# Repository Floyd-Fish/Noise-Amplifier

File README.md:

# Noise Amplifier

An ultra-low noise amplifier **(named EmoeNAP)** capable to measure low-noise LDO/OPA's wide band output noise, and many other interesting measurements. Referred to **[AN-159](https://www.analog.com/en/app-notes/an-159.html)**.

The full article about the initial version of Noise Amp can be found here:**[How to build a Noise Amplifier](https://www.emoe.xyz/noise-amplifier-building-instruction/)**. And to step further, to build the current version named **EmoeNAP**，please follow **[Noise Amplifier Step further](https://www.emoe.xyz/noise-amplifier-step-further/)**

Test result show that: with input shorted, the total output noise in 100kHz bandwidth is 1.76mVrms, and **the EmoeNAP's Gain equals to 80dB**, which results in **176nVrms input noise.**

Then connect a 50 ohms SMA Load to input, the total output noise in 100kHz bandwidth is 3.65mVrms, which equals in 365nVrms input noise.

A 50 ohms resistor's Johnson-Nyquist Noise(Themal noise) in 100kHz is 316nVrms(Theoretical), and 316nVrms combine with 176nVrms, resulting 361nVrms total output noise. This test verified the EmoeNAP's extraordinary ability to measure a 50 ohms resistor's Thermal Noise precisely.

# Still In Progress

**V2.3 has been verified but still needs improving.**    
In next version of EmoeNAP, I plan to change its architecture a little to the form below:

## V2.3 Known Issue

- Poor layout of output low-pass filter, to be re-designed.  
- Input Riso is not needed, because it introduces more thermal noise to input.(Can be seen as source impedance)  
- A resistor should be connected in series at wideband output port, because capacitive load( osilloscope input port, such as) can cause loop instability problem, so a resistor is needed to isolate the opamp output to load capacitor. A common value of 100 ohms is recommended.

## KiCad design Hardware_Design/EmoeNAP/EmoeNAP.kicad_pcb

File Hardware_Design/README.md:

# Hardware Specs

- NoiseAMP_BAT
> The battery pack for Noise Amplifier. Two 14500 Type 3.7V Li-ion Battery are used to provide ultralow power rail noise and high output current for NoiseAMP to work.

- NoiseAMP_V2.3(**Aborted**)
> The main PCB of the initial version of NoiseAMP, the current revision named EmoeNAP.

- EmoeNAP
> The current main PCB of NoiseAMP, called EmoeNAP, too.

To build a single cell EmoeNAP，**just use EmoeNAP is enough**.  
To build a 2-cell EmoeNAP, maybe you could have a look at NoiseAMP_BAT.

> Using one cell is more convenient to charge the battery, but will degrade noise performance a little bit.  
> Using two cell would get the best noise performance of EmoeNAP.

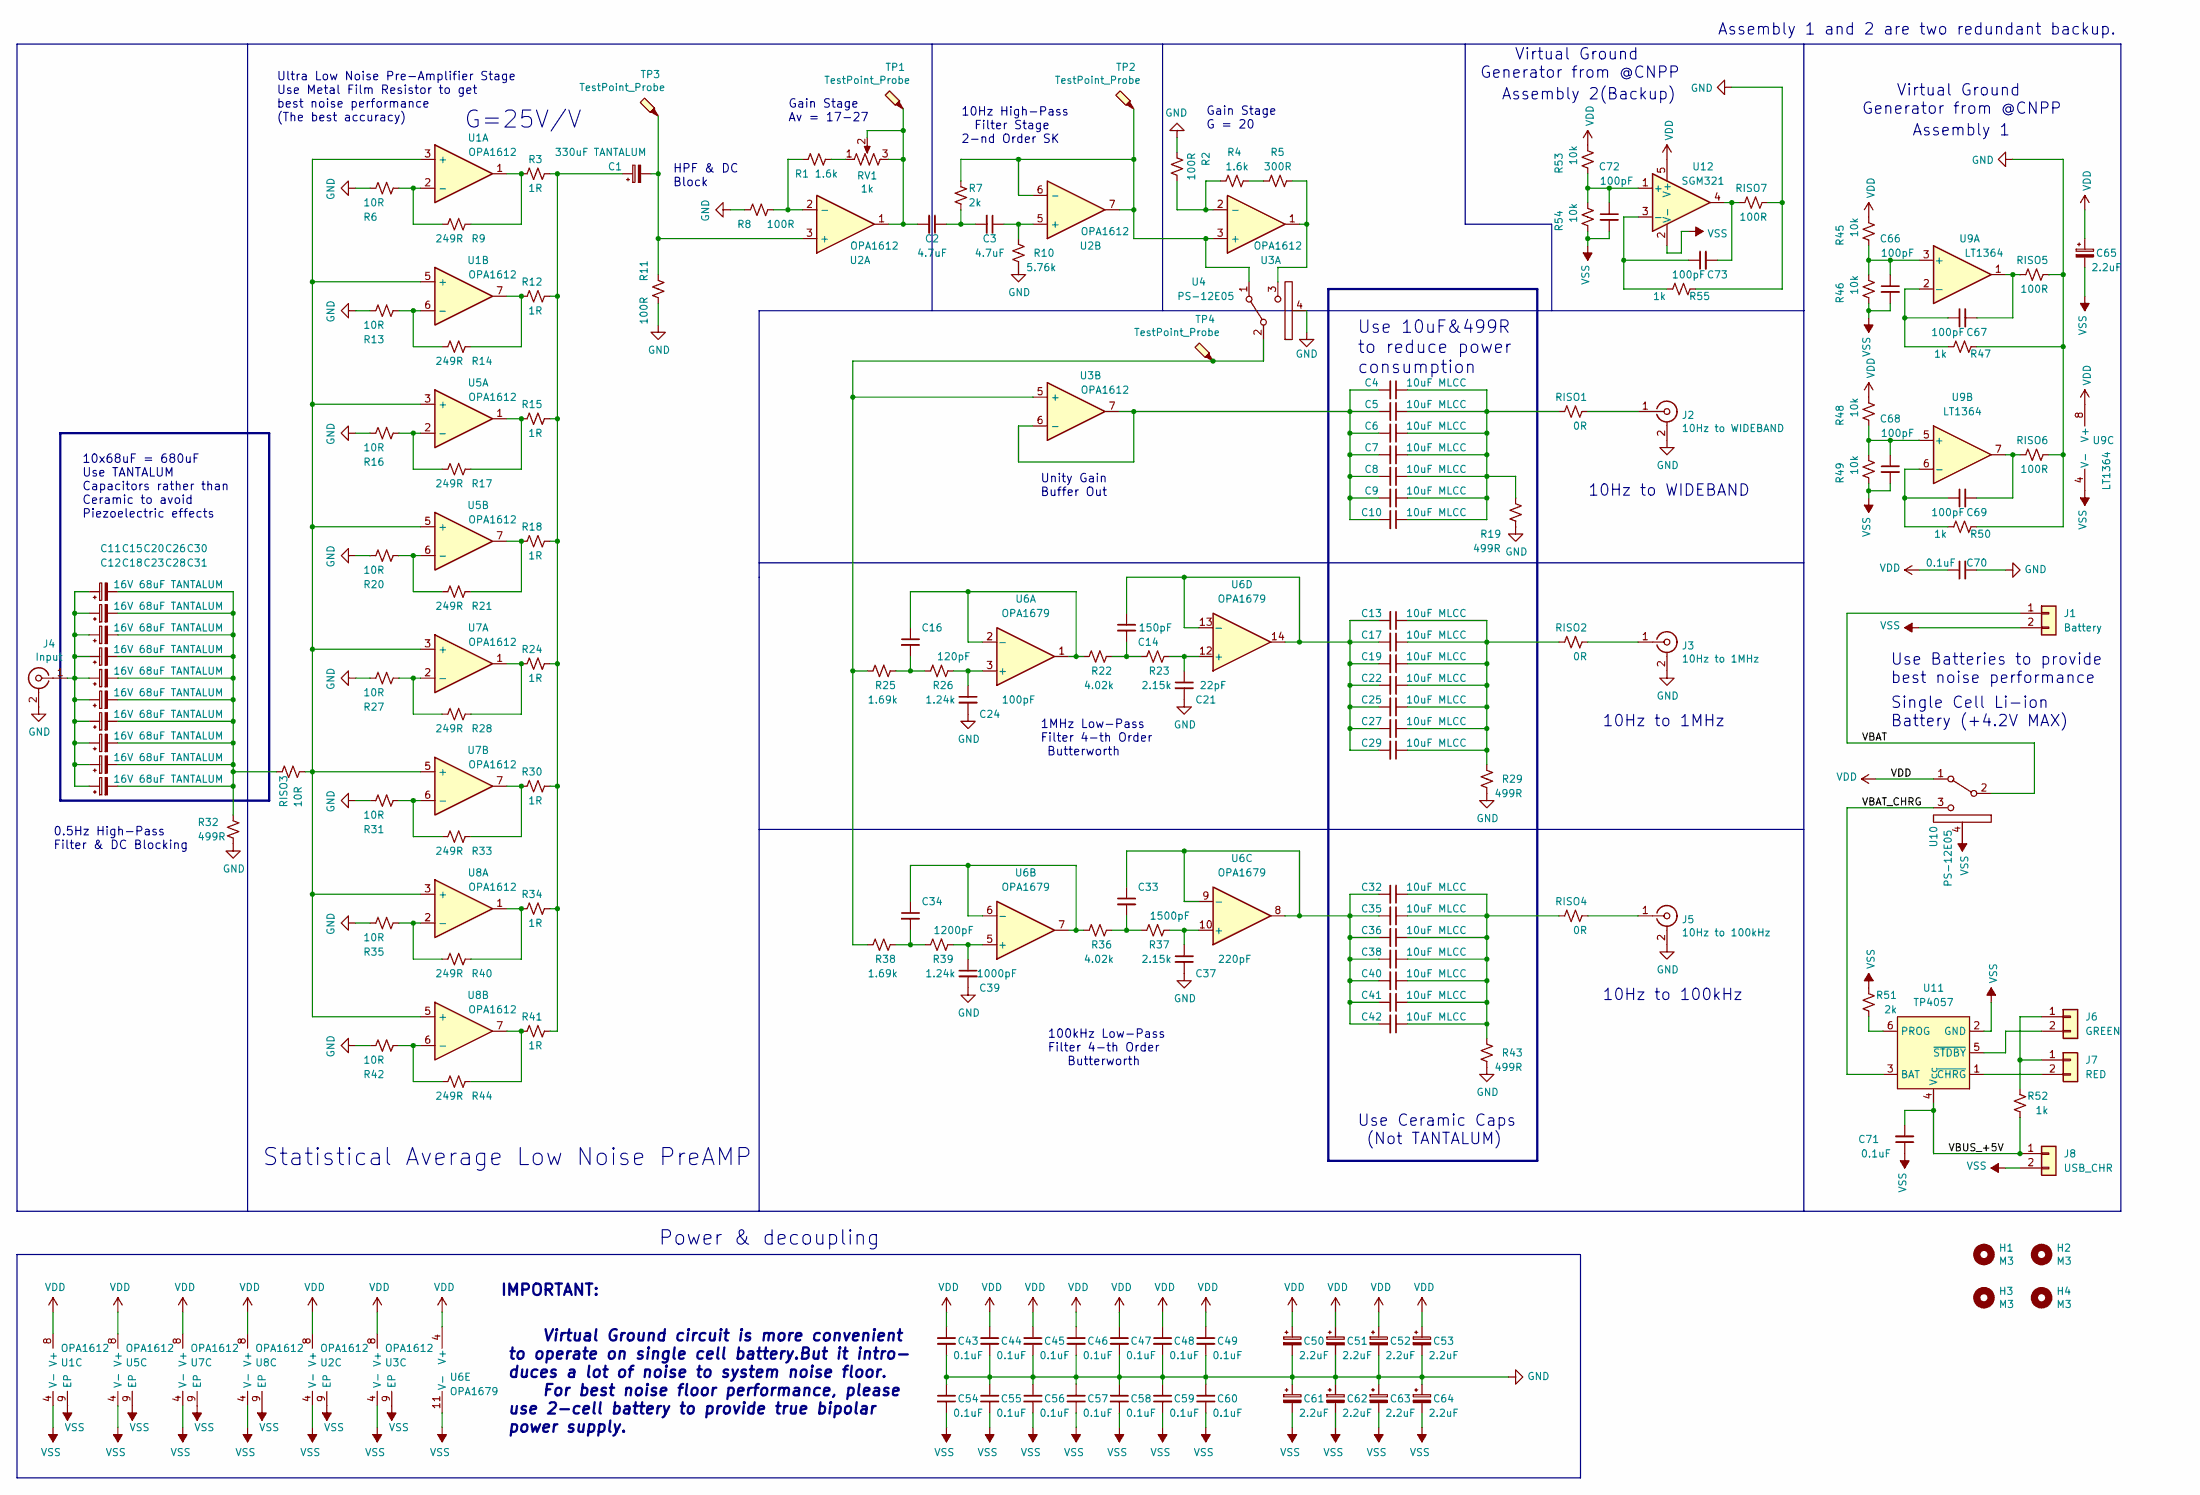
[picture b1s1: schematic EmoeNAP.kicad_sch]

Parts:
C1: 330uF TANTALUM; CP_EIA-6032-20_AVX-F
C2, C3: 4.7uF; C_0805_2012Metric
C4, C5, C6, C7, C8, C9, C10, C13, C17, C19, C22, C25, C27, C29, C32, C35, C36, C38, C40, C41, C42: 10uF MLCC; C_0805_2012Metric
C11, C12, C15, C18, C20, C23, C26, C28, C30, C31: 16V 68uF TANTALUM; CP_EIA-6032-20_AVX-F
C14: 150pF; C_0402_1005Metric
C16: 120pF; C_0402_1005Metric
C21: 22pF; C_0402_1005Metric
C24, C66, C67, C68, C69, C72, C73: 100pF; C_0402_1005Metric
C33: 1500pF; C_0402_1005Metric
C34: 1200pF; C_0402_1005Metric
C37: 220pF; C_0402_1005Metric
C39: 1000pF; C_0402_1005Metric
C43, C44, C45, C46, C47, C48, C49, C54, C55, C56, C57, C58, C59, C60, C70, C71: 0.1uF; C_0402_1005Metric
C50, C51, C52, C53, C61, C62, C63, C64, C65: 2.2uF; CP_EIA-3216-10_Kemet-I
H1, H2, H3, H4: M3; MountingHole_3.2mm_M3_Pad_TopOnly
J1: Battery; JST_XA_B02B-XASK-1_1x02_P2.50mm_Vertical
J2: 10Hz to WIDEBAND; U.FL_Molex_MCRF_73412-0110_Vertical
J3: 10Hz to 1MHz; U.FL_Molex_MCRF_73412-0110_Vertical
J4: Input; U.FL_Molex_MCRF_73412-0110_Vertical
J5: 10Hz to 100kHz; U.FL_Molex_MCRF_73412-0110_Vertical
J6: GREEN; TestPoint_2Pads_Pitch2.54mm_Drill0.8mm
J7: RED; TestPoint_2Pads_Pitch2.54mm_Drill0.8mm
J8: USB_CHR; JST_XA_B02B-XASK-1_1x02_P2.50mm_Vertical
R1, R4: 1.6k; R_0402_1005Metric
R2, R8, R11: 100R; R_0402_1005Metric
R3, R12, R15, R18, R24, R30, R34, R41: 1R; R_0402_1005Metric
R5: 300R; R_0402_1005Metric
R6, R13, R16, R20, R27, R31, R35, R42: 10R; R_0402_1005Metric
R7, R51: 2k; R_0402_1005Metric
R9, R14, R17, R21, R28, R33, R40, R44: 249R; R_0402_1005Metric
R10: 5.76k; R_0402_1005Metric
R19, R29, R32, R43: 499R; R_0805_2012Metric
R22, R36: 4.02k; R_0402_1005Metric
R23, R37: 2.15k; R_0402_1005Metric
R25, R38: 1.69k; R_0402_1005Metric
R26, R39: 1.24k; R_0402_1005Metric
R45, R46, R48, R49, R53, R54: 10k; R_0402_1005Metric
R47, R50, R52, R55: 1k; R_0402_1005Metric
RISO1, RISO2, RISO4: 0R; R_0805_2012Metric
RISO3: 10R; R_0805_2012Metric
RISO5, RISO6, RISO7: 100R; R_0603_1608Metric
RV1: 1k; Potentiometer_Bourns_3266W_Vertical
TP1, TP2, TP3, TP4: TestPoint_Probe; TestPoint_Pad_D1.0mm
U1, U2, U3, U5, U7, U8: OPA1612; WSON-8-1EP_3x3mm_P0.5mm_EP1.2x2mm
U4, U10: PS-12E05
U6: OPA1679; SOIC-14_3.9x8.7mm_P1.27mm
U9: LT1364; SOIC-8_3.9x4.9mm_P1.27mm
U11: TP4057; SOT-23-6
U12: SGM321; SOT-23-5

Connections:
/VBAT: J1.1, U10.2
/VBAT_CHRG: U10.3, U11.3 (BAT)
/VBUS_+5V: C71.2, J8.1, R52.1, U11.4 (Vcc)
GND: C21.2, C24.2, C37.2, C39.2, C43.2, C44.2, C45.2, C46.2, C47.2, C48.2, C49.2, C50.2, C51.2, C52.2, C53.2, C54.1, C55.1, C56.1, C57.1, C58.1, C59.1, C60.1, C61.1, C62.1, C63.1, C64.1, C70.2, J2.2 (Ext), J3.2 (Ext), J4.2 (Ext), J5.2 (Ext), R2.1, R6.2, R8.1, R10.2, R11.2, R13.2, R16.2, R19.2, R20.2, R27.2, R29.2, R31.2, R32.2, R35.2, R42.2, R43.2, R47.1, R50.1, R55.1, RISO5.2, RISO6.2, RISO7.2, U4.4
unnamed: C1.1, R3.2, R12.2, R15.2, R18.2, R24.2, R30.2, R34.2, R41.2
unnamed: C1.2, R11.1, TP3.1, U2.3 (+)
unnamed: C2.1, C3.2, R7.2
unnamed: C2.2, RV1.2, RV1.3, TP1.1, U2.1
unnamed: C3.1, R10.1, U2.5 (+)
unnamed: C4.1, C5.1, C6.1, C7.1, C8.1, C9.1, C10.1, R19.1, RISO1.1
unnamed: C4.2, C5.2, C6.2, C7.2, C8.2, C9.2, C10.2, U3.6 (-), U3.7
unnamed: C11.1, C12.1, C15.1, C18.1, C20.1, C23.1, C26.1, C28.1, C30.1, C31.1, J4.1 (In)
unnamed: C11.2, C12.2, C15.2, C18.2, C20.2, C23.2, C26.2, C28.2, C30.2, C31.2, R32.1, RISO3.1
unnamed: C13.1, C17.1, C19.1, C22.1, C25.1, C27.1, C29.1, R29.1, RISO2.1
unnamed: C13.2, C14.1, C17.2, C19.2, C22.2, C25.2, C27.2, C29.2, U6.13 (-), U6.14
unnamed: C14.2, R22.1, R23.2
unnamed: C16.1, R22.2, U6.1, U6.2 (-)
unnamed: C16.2, R25.1, R26.2
unnamed: C21.1, R23.1, U6.12 (+)
unnamed: C24.1, R26.1, U6.3 (+)
unnamed: C32.1, C35.1, C36.1, C38.1, C40.1, C41.1, C42.1, R43.1, RISO4.1
unnamed: C32.2, C33.1, C35.2, C36.2, C38.2, C40.2, C41.2, C42.2, U6.8, U6.9 (-)
unnamed: C33.2, R36.1, R37.2
unnamed: C34.1, R36.2, U6.6 (-), U6.7
unnamed: C34.2, R38.1, R39.2
unnamed: C37.1, R37.1, U6.10 (+)
unnamed: C39.1, R39.1, U6.5 (+)
unnamed: C66.1, R45.1, R46.2, U9.3 (+)
unnamed: C67.1, R47.2, U9.2 (-)
unnamed: C67.2, RISO5.1, U9.1
unnamed: C68.1, R48.1, R49.2, U9.5 (+)
unnamed: C69.1, R50.2, U9.6 (-)
unnamed: C69.2, RISO6.1, U9.7
unnamed: C72.1, R53.1, R54.2, U12.1 (+)
unnamed: C73.1, R55.2, U12.3 (-)
unnamed: C73.2, RISO7.1, U12.4
unnamed: J2.1 (In), RISO1.2
unnamed: J3.1 (In), RISO2.2
unnamed: J5.1 (In), RISO4.2
unnamed: J6.1, J7.1, R52.2
unnamed: J6.2, U11.5 (~STDBY)
unnamed: J7.2, U11.1 (~CHRG)
unnamed: R1.1, R8.2, U2.2 (-)
unnamed: R1.2, RV1.1
unnamed: R2.2, R4.1, U3.2 (-)
unnamed: R3.1, R9.1, U1.1
unnamed: R4.2, R5.1
unnamed: R5.2, U3.1, U4.3
unnamed: R6.1, R9.2, U1.2 (-)
unnamed: R7.1, TP2.1, U2.6 (-), U2.7, U3.3 (+), U4.1
unnamed: R12.1, R14.1, U1.7
unnamed: R13.1, R14.2, U1.6 (-)
unnamed: R15.1, R17.1, U5.1
unnamed: R16.1, R17.2, U5.2 (-)
unnamed: R18.1, R21.1, U5.7
unnamed: R20.1, R21.2, U5.6 (-)
unnamed: R24.1, R28.1, U7.1
unnamed: R25.2, R38.2, TP4.1, U3.5 (+), U4.2
unnamed: R27.1, R28.2, U7.2 (-)
unnamed: R30.1, R33.1, U7.7
unnamed: R31.1, R33.2, U7.6 (-)
unnamed: R34.1, R40.1, U8.1
unnamed: R35.1, R40.2, U8.2 (-)
unnamed: R41.1, R44.1, U8.7
unnamed: R42.1, R44.2, U8.6 (-)
unnamed: R51.1, U11.6 (PROG)
unnamed: RISO3.2, U1.3 (+), U1.5 (+), U5.3 (+), U5.5 (+), U7.3 (+), U7.5 (+), U8.3 (+), U8.5 (+)
VDD: C43.1, C44.1, C45.1, C46.1, C47.1, C48.1, C49.1, C50.1, C51.1, C52.1, C53.1, C65.1, C70.1, R45.2, R48.2, R53.2, U1.8 (V+), U2.8 (V+), U3.8 (V+), U5.8 (V+), U6.4 (V+), U7.8 (V+), U8.8 (V+), U9.8 (V+), U10.1, U12.5 (V+)
VSS: C54.2, C55.2, C56.2, C57.2, C58.2, C59.2, C60.2, C61.2, C62.2, C63.2, C64.2, C65.2, C66.2, C68.2, C71.1, C72.2, J1.2, J8.2, R46.1, R49.1, R51.2, R54.1, U1.4 (V-), U1.9 (EP), U2.4 (V-), U2.9 (EP), U3.4 (V-), U3.9 (EP), U5.4 (V-), U5.9 (EP), U6.11 (V-), U7.4 (V-), U7.9 (EP), U8.4 (V-), U8.9 (EP), U9.4 (V-), U10.4, U11.2 (GND), U12.2 (V-)

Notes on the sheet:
100kHz Low-Pass Filter 4-th Order Butterworth
Use 10uF&499R to reduce power consumption
Single Cell Li-ion Battery (+4.2V MAX)
0.5Hz High-Pass Filter & DC Blocking
10x68uF = 680uF Use TANTALUM Capacitors rather than Ceramic to avoid Piezoelectric effects
Statistical Average Low Noise PreAMP
G=25V/V
1MHz Low-Pass Filter 4-th Order Butterworth
HPF & DC Block
Virtual Ground Generator from @CNPP
10Hz to 100kHz
Assembly 2(Backup)
Use Batteries to provide best noise performance
10Hz High-Pass Filter Stage 2-nd Order SK
Power & decoupling
Unity Gain Buffer Out
IMPORTANT:
Ultra Low Noise Pre-Amplifier Stage Use Metal Film Resistor to get best noise performance (The best accuracy)
10Hz to 1MHz
Virtual Ground circuit is more convenient to operate on single cell battery.But it intro- duces a lot of noise to system noise floor. For best noise floor performance, please use 2-cell battery to provide true bipolar power supply.
10Hz to WIDEBAND
Use Ceramic Caps (Not TANTALUM)
Assembly 1 and 2 are two redundant backup.
Gain Stage G = 20
Gain Stage Av = 17-27
Assembly 1

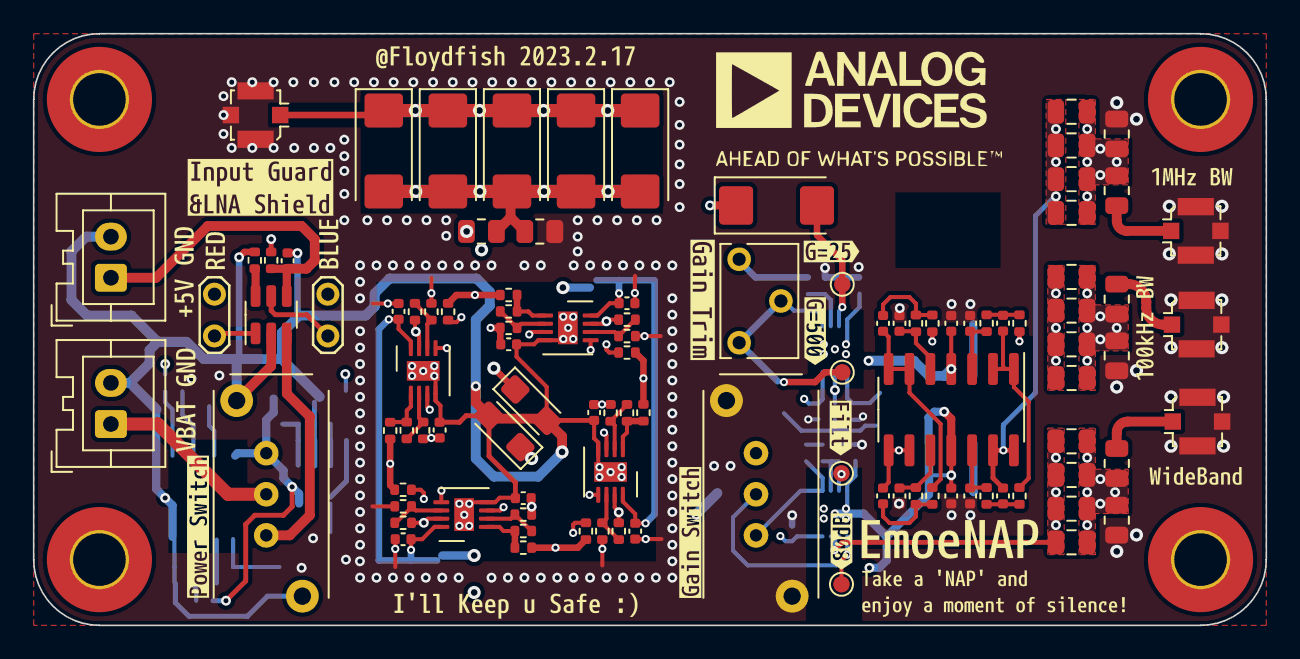
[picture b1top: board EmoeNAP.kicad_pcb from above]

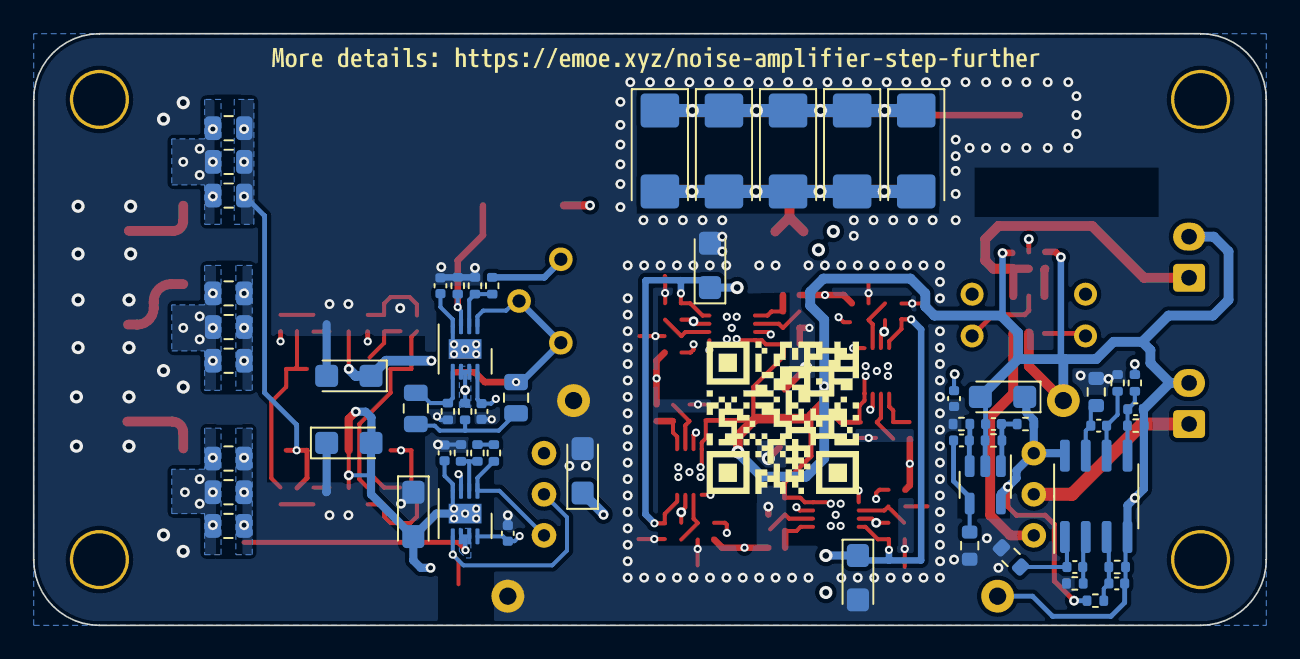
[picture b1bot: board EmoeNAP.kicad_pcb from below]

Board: 4 copper layers, 75.0 x 36.0 mm, 184 parts (59 on the bottom side), 69 nets.

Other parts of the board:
kibuzzard-63ED0A5F: G***; kibuzzard-63ED0A5F
kibuzzard-63EE51C1: G***; kibuzzard-63EE51C1
kibuzzard-63EE51DC: G***; kibuzzard-63EE51DC
kibuzzard-63EE53DB: G***; kibuzzard-63EE53DB
kibuzzard-63EE512D: G***; kibuzzard-63EE512D
kibuzzard-63EE520C: G***; kibuzzard-63EE520C
kibuzzard-63EE5216: G***; kibuzzard-63EE5216
kibuzzard-63EE5345: G***; kibuzzard-63EE5345
kibuzzard-6378A7DC: G***; kibuzzard-6378A7DC
kibuzzard-6378A7EA: G***; kibuzzard-6378A7EA
kibuzzard-6378A7F5: G***; kibuzzard-6378A7F5
kibuzzard-6378A8E8: G***; kibuzzard-6378A8E8
kibuzzard-6378A91A: G***; kibuzzard-6378A91A
kibuzzard-6378A94A: G***; kibuzzard-6378A94A
kibuzzard-6378A590: G***; kibuzzard-6378A590
kibuzzard-6378A691: G***; kibuzzard-6378A691
kibuzzard-6378A997: G***; kibuzzard-6378A997
kibuzzard-6378AA98: G***; kibuzzard-6378AA98
kibuzzard-6378AAC6: G***; kibuzzard-6378AAC6
kibuzzard-6378AB16: G***; kibuzzard-6378AB16

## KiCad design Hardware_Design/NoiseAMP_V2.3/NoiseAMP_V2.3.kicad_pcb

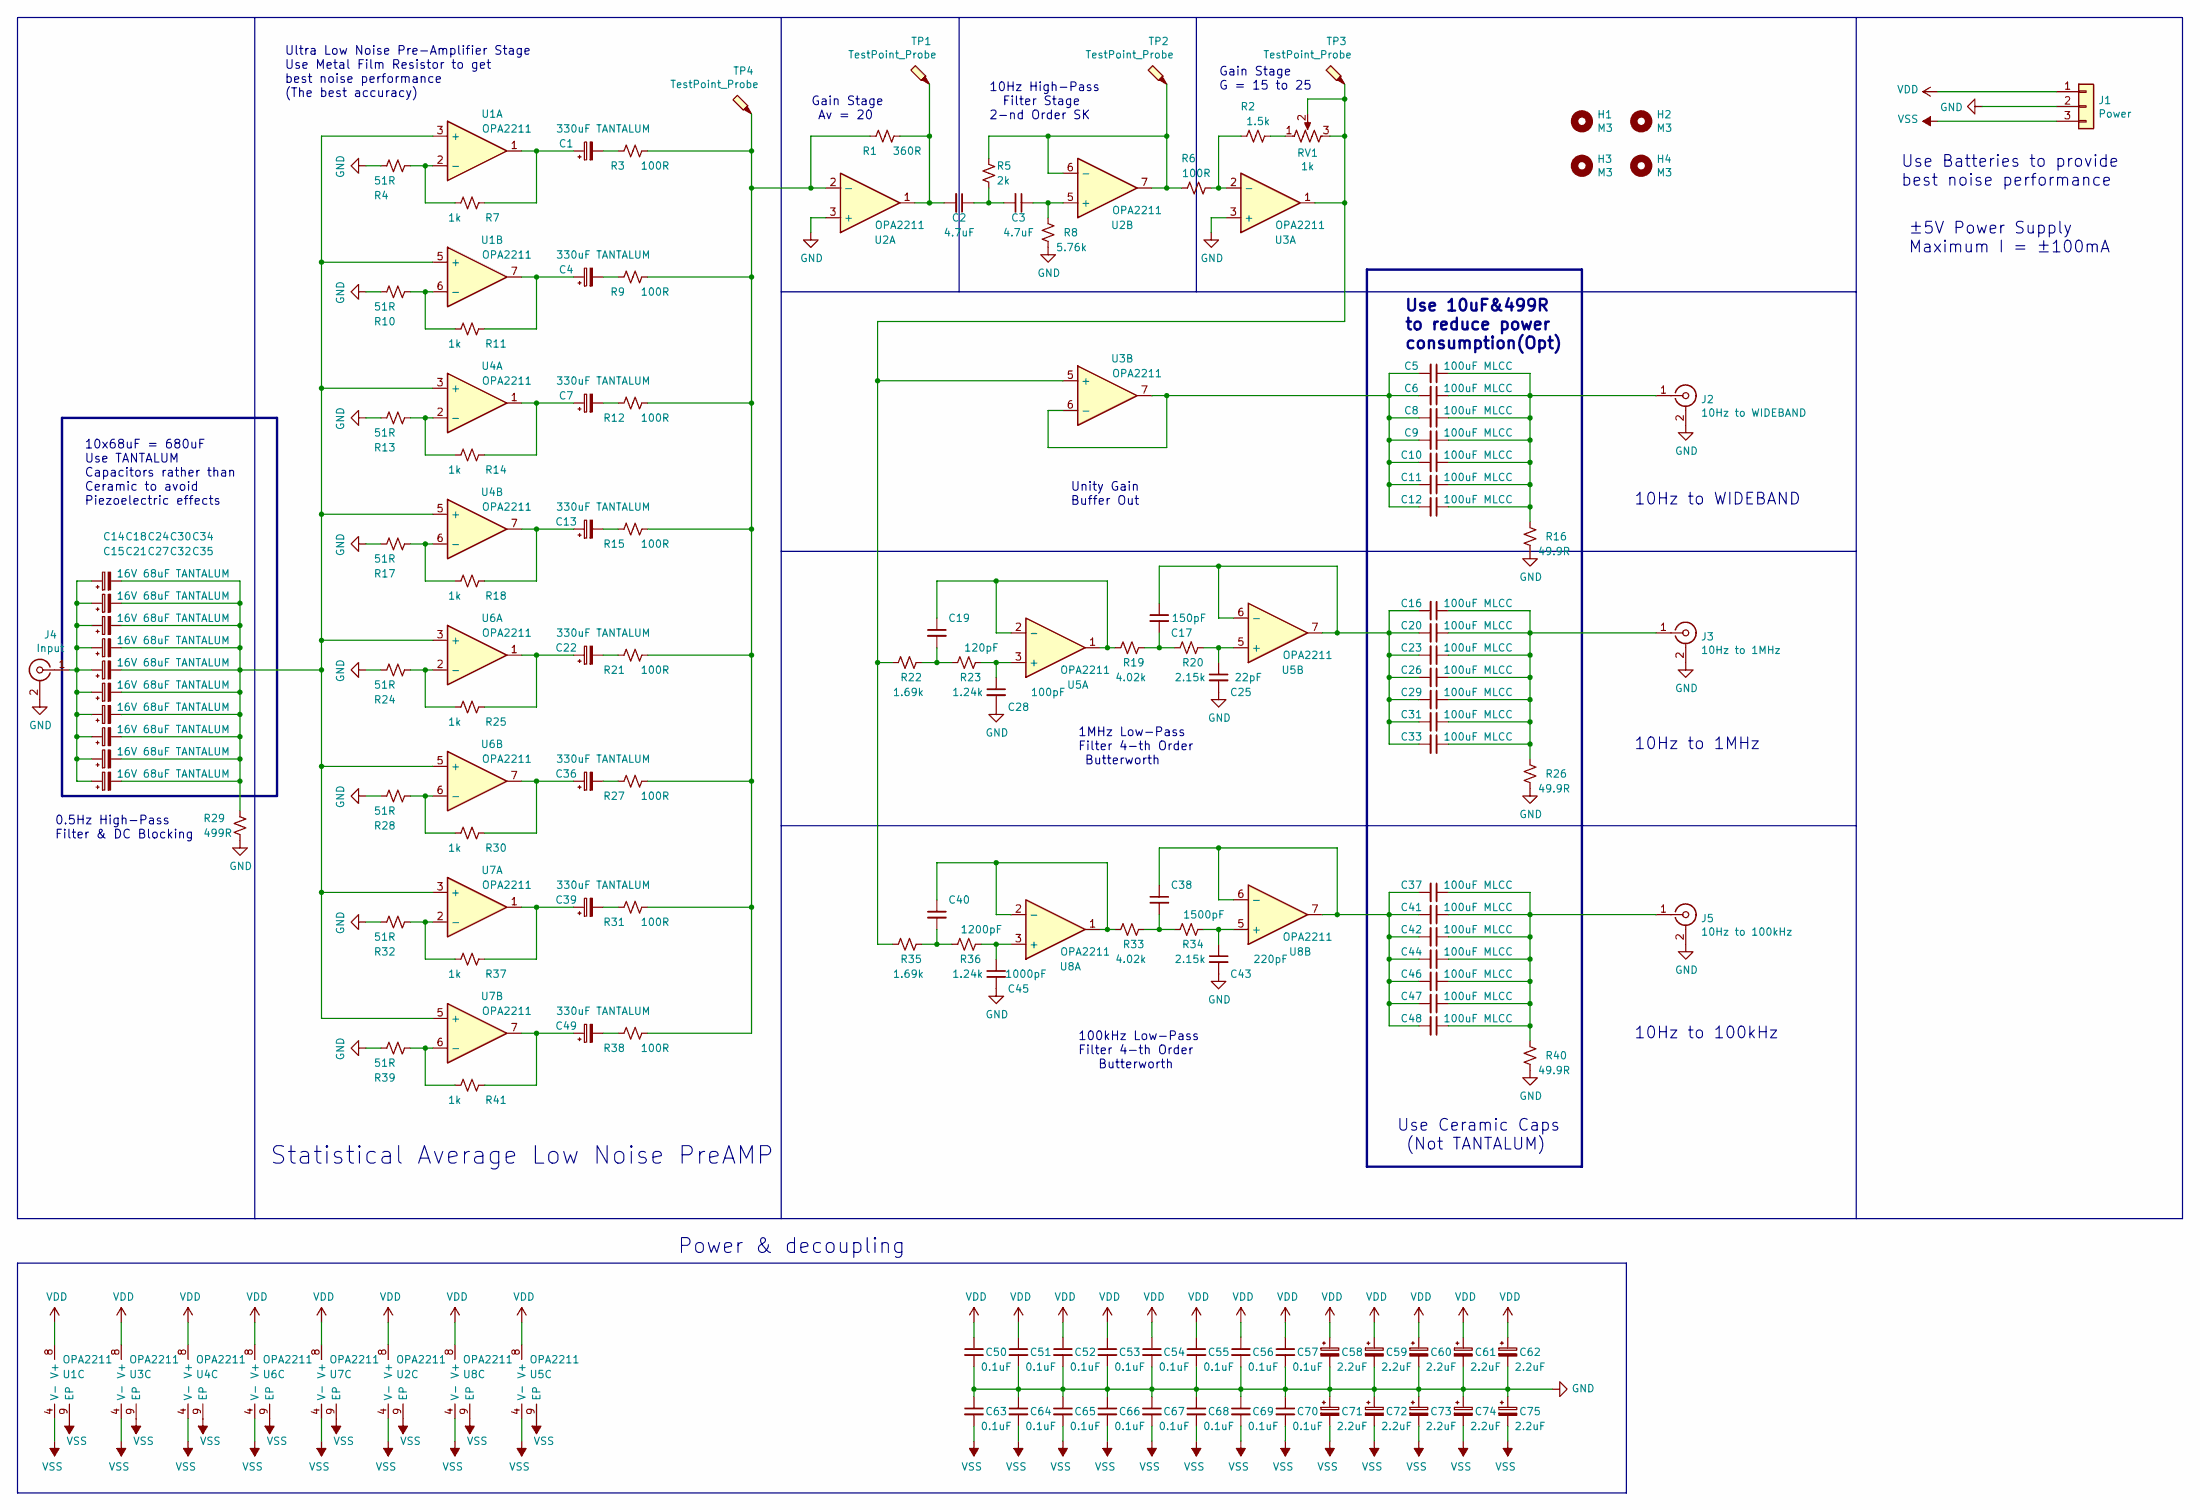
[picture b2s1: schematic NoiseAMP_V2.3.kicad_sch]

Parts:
C1, C4, C7, C13, C22, C36, C39, C49: 330uF TANTALUM; CP_EIA-6032-20_AVX-F
C2, C3: 4.7uF; C_0805_2012Metric
C5, C6, C8, C9, C10, C11, C12, C16, C20, C23, C26, C29, C31, C33, C37, C41, C42, C44, C46, C47, C48: 100uF MLCC; C_1206_3216Metric
C14, C15, C18, C21, C24, C27, C30, C32, C34, C35: 16V 68uF TANTALUM; CP_EIA-6032-20_AVX-F
C17: 150pF; C_0402_1005Metric
C19: 120pF; C_0402_1005Metric
C25: 22pF; C_0402_1005Metric
C28: 100pF; C_0402_1005Metric
C38: 1500pF; C_0402_1005Metric
C40: 1200pF; C_0402_1005Metric
C43: 220pF; C_0402_1005Metric
C45: 1000pF; C_0402_1005Metric
C50, C51, C52, C53, C54, C55, C56, C57, C63, C64, C65, C66, C67, C68, C69, C70: 0.1uF; C_0402_1005Metric
C58, C59, C60, C61, C62, C71, C72, C73, C74, C75: 2.2uF; CP_EIA-3216-10_Kemet-I
H1, H2, H3, H4: M3; MountingHole_3.2mm_M3_Pad_TopOnly
J1: Power; JST_XH_B3B-XH-A_1x03_P2.50mm_Vertical
J2: 10Hz to WIDEBAND; U.FL_Molex_MCRF_73412-0110_Vertical
J3: 10Hz to 1MHz; U.FL_Molex_MCRF_73412-0110_Vertical
J4: Input; U.FL_Molex_MCRF_73412-0110_Vertical
J5: 10Hz to 100kHz; U.FL_Molex_MCRF_73412-0110_Vertical
R1: 360R; R_0402_1005Metric
R2: 1.5k; R_0402_1005Metric
R3, R6, R9, R12, R15, R21, R27, R31, R38: 100R; R_0402_1005Metric
R4, R10, R13, R17, R24, R28, R32, R39: 51R; R_0402_1005Metric
R5: 2k; R_0402_1005Metric
R7, R11, R14, R18, R25, R30, R37, R41: 1k; R_0402_1005Metric
R8: 5.76k; R_0402_1005Metric
R16, R26, R40: 49.9R; R_0402_1005Metric
R19, R33: 4.02k; R_0402_1005Metric
R20, R34: 2.15k; R_0402_1005Metric
R22, R35: 1.69k; R_0402_1005Metric
R23, R36: 1.24k; R_0402_1005Metric
R29: 499R; R_0402_1005Metric
RV1: 1k; Potentiometer_Bourns_3296W_Vertical
TP1, TP2, TP3, TP4: TestPoint_Probe; TestPoint_Pad_D1.0mm
U1, U2, U3, U4, U5, U6, U7, U8: OPA2211; WSON-8-1EP_3x3mm_P0.5mm_EP1.2x2mm

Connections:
GND: C25.2, C28.2, C43.2, C45.2, C50.2, C51.2, C52.2, C53.2, C54.2, C55.2, C56.2, C57.2, C58.2, C59.2, C60.2, C61.2, C62.2, C63.1, C64.1, C65.1, C66.1, C67.1, C68.1, C69.1, C70.1, C71.1, C72.1, C73.1, C74.1, C75.1, J1.2, J2.2 (Ext), J3.2 (Ext), J4.2 (Ext), J5.2 (Ext), R4.2, R8.2, R10.2, R13.2, R16.2, R17.2, R24.2, R26.2, R28.2, R29.2, R32.2, R39.2, R40.2, U2.3 (+), U3.3 (+)
unnamed: C1.1, R7.1, U1.1
unnamed: C1.2, R3.1
unnamed: C2.1, C3.2, R5.2
unnamed: C2.2, R1.2, TP1.1, U2.1
unnamed: C3.1, R8.1, U2.5 (+)
unnamed: C4.1, R11.1, U1.7
unnamed: C4.2, R9.1
unnamed: C7.1, R14.1, U4.1
unnamed: C7.2, R12.1
unnamed: C5.1, C6.1, C8.1, C9.1, C10.1, C11.1, C12.1, J2.1 (In), R16.1
unnamed: C5.2, C6.2, C8.2, C9.2, C10.2, C11.2, C12.2, U3.6 (-), U3.7
unnamed: C13.1, R18.1, U4.7
unnamed: C13.2, R15.1
unnamed: C14.1, C15.1, C18.1, C21.1, C24.1, C27.1, C30.1, C32.1, C34.1, C35.1, J4.1 (In)
unnamed: C14.2, C15.2, C18.2, C21.2, C24.2, C27.2, C30.2, C32.2, C34.2, C35.2, R29.1, U1.3 (+), U1.5 (+), U4.3 (+), U4.5 (+), U6.3 (+), U6.5 (+), U7.3 (+), U7.5 (+)
unnamed: C16.1, C20.1, C23.1, C26.1, C29.1, C31.1, C33.1, J3.1 (In), R26.1
unnamed: C16.2, C17.1, C20.2, C23.2, C26.2, C29.2, C31.2, C33.2, U5.6 (-), U5.7
unnamed: C17.2, R19.1, R20.2
unnamed: C19.1, R19.2, U5.1, U5.2 (-)
unnamed: C19.2, R22.1, R23.2
unnamed: C22.1, R25.1, U6.1
unnamed: C22.2, R21.1
unnamed: C25.1, R20.1, U5.5 (+)
unnamed: C28.1, R23.1, U5.3 (+)
unnamed: C36.1, R30.1, U6.7
unnamed: C36.2, R27.1
unnamed: C37.1, C41.1, C42.1, C44.1, C46.1, C47.1, C48.1, J5.1 (In), R40.1
unnamed: C37.2, C38.1, C41.2, C42.2, C44.2, C46.2, C47.2, C48.2, U8.6 (-), U8.7
unnamed: C38.2, R33.1, R34.2
unnamed: C39.1, R37.1, U7.1
unnamed: C39.2, R31.1
unnamed: C40.1, R33.2, U8.1, U8.2 (-)
unnamed: C40.2, R35.1, R36.2
unnamed: C43.1, R34.1, U8.5 (+)
unnamed: C45.1, R36.1, U8.3 (+)
unnamed: C49.1, R41.1, U7.7
unnamed: C49.2, R38.1
unnamed: R1.1, R3.2, R9.2, R12.2, R15.2, R21.2, R27.2, R31.2, R38.2, TP4.1, U2.2 (-)
unnamed: R2.1, R6.2, U3.2 (-)
unnamed: R2.2, RV1.1
unnamed: R4.1, R7.2, U1.2 (-)
unnamed: R5.1, R6.1, TP2.1, U2.6 (-), U2.7
unnamed: R10.1, R11.2, U1.6 (-)
unnamed: R13.1, R14.2, U4.2 (-)
unnamed: R17.1, R18.2, U4.6 (-)
unnamed: R22.2, R35.2, RV1.2, RV1.3, TP3.1, U3.1, U3.5 (+)
unnamed: R24.1, R25.2, U6.2 (-)
unnamed: R28.1, R30.2, U6.6 (-)
unnamed: R32.1, R37.2, U7.2 (-)
unnamed: R39.1, R41.2, U7.6 (-)
VDD: C50.1, C51.1, C52.1, C53.1, C54.1, C55.1, C56.1, C57.1, C58.1, C59.1, C60.1, C61.1, C62.1, J1.1, U1.8 (V+), U2.8 (V+), U3.8 (V+), U4.8 (V+), U5.8 (V+), U6.8 (V+), U7.8 (V+), U8.8 (V+)
VSS: C63.2, C64.2, C65.2, C66.2, C67.2, C68.2, C69.2, C70.2, C71.2, C72.2, C73.2, C74.2, C75.2, J1.3, U1.4 (V-), U1.9 (EP), U2.4 (V-), U2.9 (EP), U3.4 (V-), U3.9 (EP), U4.4 (V-), U4.9 (EP), U5.4 (V-), U5.9 (EP), U6.4 (V-), U6.9 (EP), U7.4 (V-), U7.9 (EP), U8.4 (V-), U8.9 (EP)

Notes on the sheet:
100kHz Low-Pass Filter 4-th Order Butterworth
Use 10uF&499R to reduce power consumption(Opt)
0.5Hz High-Pass Filter & DC Blocking
10x68uF = 680uF Use TANTALUM Capacitors rather than Ceramic to avoid Piezoelectric effects
Statistical Average Low Noise PreAMP
1MHz Low-Pass Filter 4-th Order Butterworth
10Hz to 100kHz
10Hz High-Pass Filter Stage 2-nd Order SK
Power & decoupling
Unity Gain Buffer Out
Use Batteries to provide best noise performance
Ultra Low Noise Pre-Amplifier Stage Use Metal Film Resistor to get best noise performance (The best accuracy)
10Hz to 1MHz
±5V Power Supply Maximum I = ±100mA
10Hz to WIDEBAND
Use Ceramic Caps (Not TANTALUM)
Gain Stage G = 15 to 25
Gain Stage Av = 20

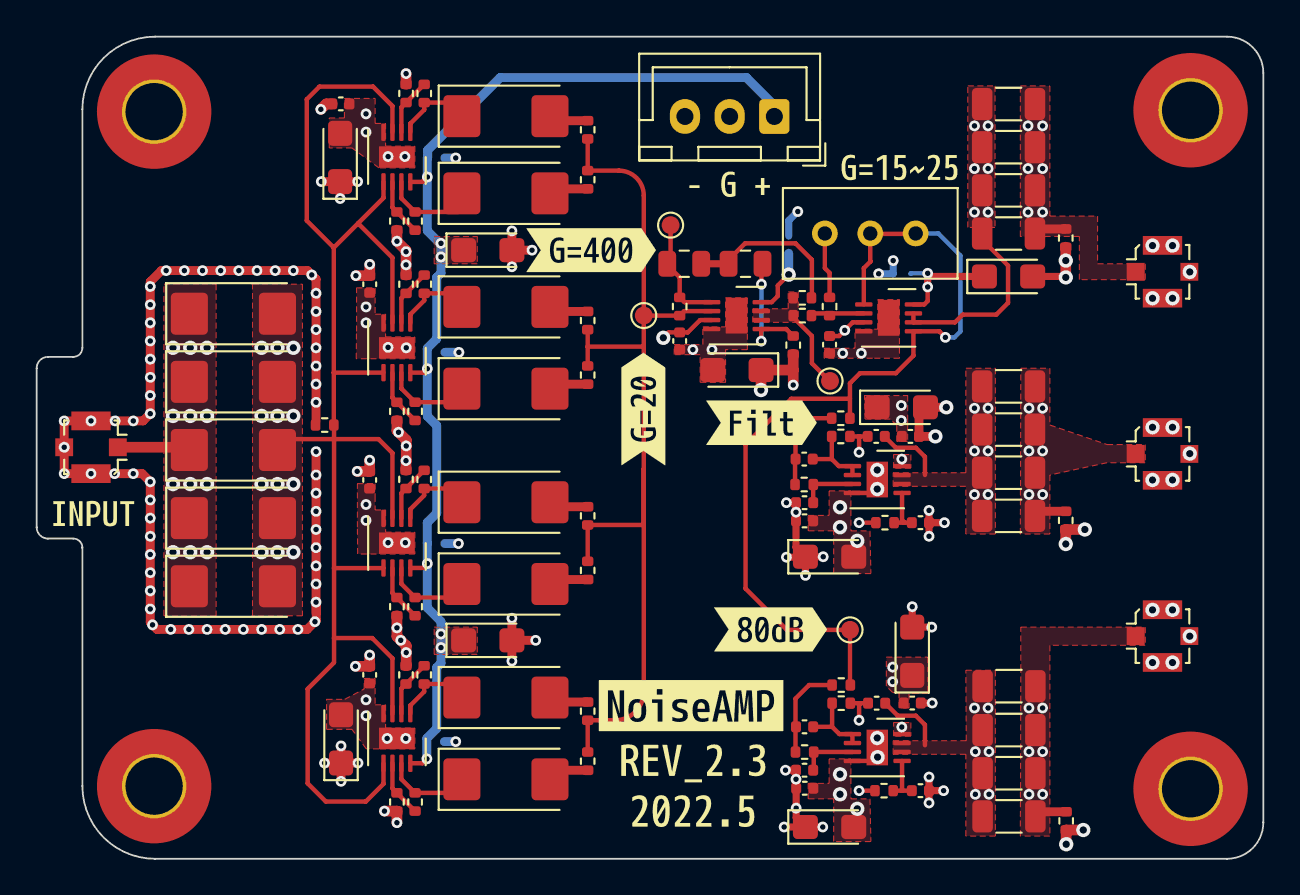
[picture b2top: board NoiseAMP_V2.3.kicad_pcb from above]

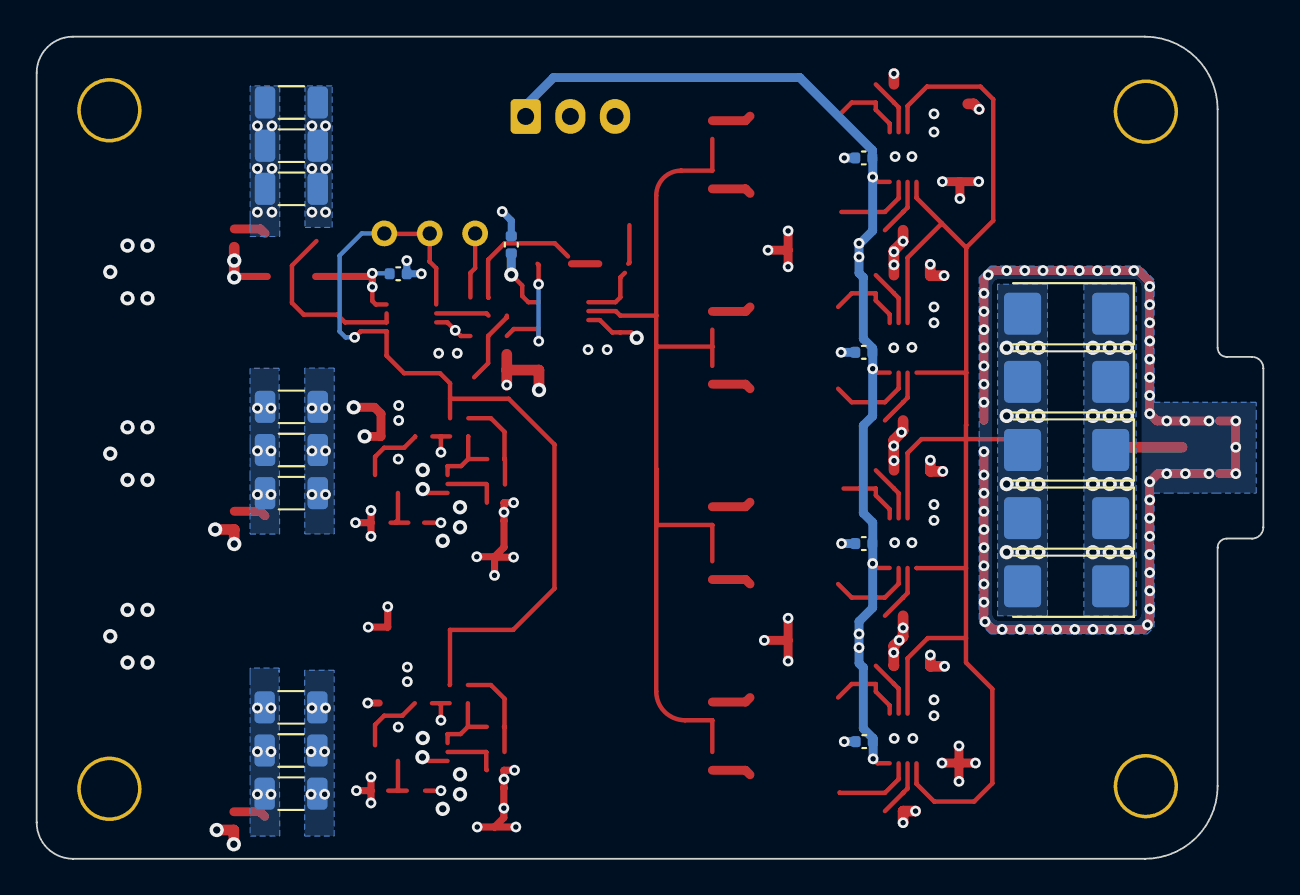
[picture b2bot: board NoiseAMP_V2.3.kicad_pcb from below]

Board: 4 copper layers, 68.6 x 46.0 mm, 148 parts (20 on the bottom side), 53 nets.

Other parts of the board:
kibuzzard-62753A7A: G***; kibuzzard-62753A7A
kibuzzard-62753A96: G***; kibuzzard-62753A96
kibuzzard-6238052E: G***; kibuzzard-6238052E
kibuzzard-6238054F: G***; kibuzzard-6238054F
kibuzzard-6238081A: G***; kibuzzard-6238081A
kibuzzard-6275398E: G***; kibuzzard-6275398E
kibuzzard-62380362: G***; kibuzzard-62380362
kibuzzard-62380566: G***; kibuzzard-62380566
kibuzzard-62380599: G***; kibuzzard-62380599
kibuzzard-62380883: G***; kibuzzard-62380883

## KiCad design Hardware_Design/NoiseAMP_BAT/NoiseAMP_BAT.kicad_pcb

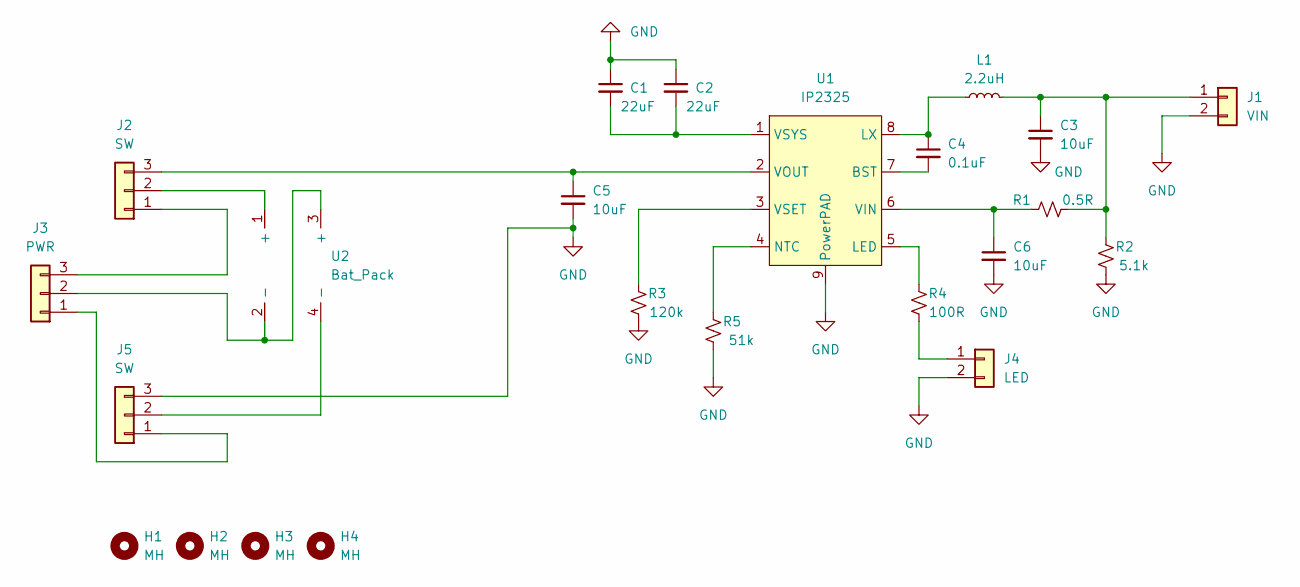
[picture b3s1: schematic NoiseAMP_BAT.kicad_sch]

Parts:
C1, C2: 22uF; C_1206_3216Metric
C3, C5, C6: 10uF; C_1206_3216Metric
C4: 0.1uF; C_0805_2012Metric
H1, H2, H3, H4: MH; MountingHole_3.2mm_M3_ISO7380
J1: VIN; JST_XA_B02B-XASK-1_1x02_P2.50mm_Vertical
J2, J5: SW; JST_XA_B03B-XASK-1_1x03_P2.50mm_Vertical
J3: PWR; JST_XA_B03B-XASK-1_1x03_P2.50mm_Vertical
J4: LED; JST_XA_B02B-XASK-1_1x02_P2.50mm_Vertical
L1: 2.2uH; L_Sumida_CDMC6D28_7.25x6.5mm
R1: 0.5R; R_0805_2012Metric
R2: 5.1k; R_0805_2012Metric
R3: 120k; R_0805_2012Metric
R4: 100R; R_0805_2012Metric
R5: 51k; R_0805_2012Metric
U1: IP2325; SOIC-8-1EP_3.9x4.9mm_P1.27mm_EP2.29x3mm
U2: Bat_Pack; 2AA_CELL

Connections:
GND: C1.1, C2.1, C3.2, C5.2, C6.2, J1.2, J4.2, J5.3, R2.1, R3.1, R5.1, U1.9 (PowerPAD)
unnamed: C1.2, C2.2, U1.1 (VSYS)
unnamed: C4.1, L1.1, U1.8 (LX)
unnamed: C4.2, U1.7 (BST)
unnamed: C5.1, J2.3, U1.2 (VOUT)
unnamed: C6.1, R1.1, U1.6 (VIN)
unnamed: J2.1, J3.3
unnamed: J2.2, U2.1 (+)
unnamed: J3.1, J5.1
unnamed: J3.2, U2.2 (-), U2.3 (+)
unnamed: J4.1, R4.1
unnamed: J5.2, U2.4 (-)
unnamed: C3.1, J1.1, L1.2, R1.2, R2.2
unnamed: R3.2, U1.3 (VSET)
unnamed: R4.2, U1.5 (LED)
unnamed: R5.2, U1.4 (NTC)

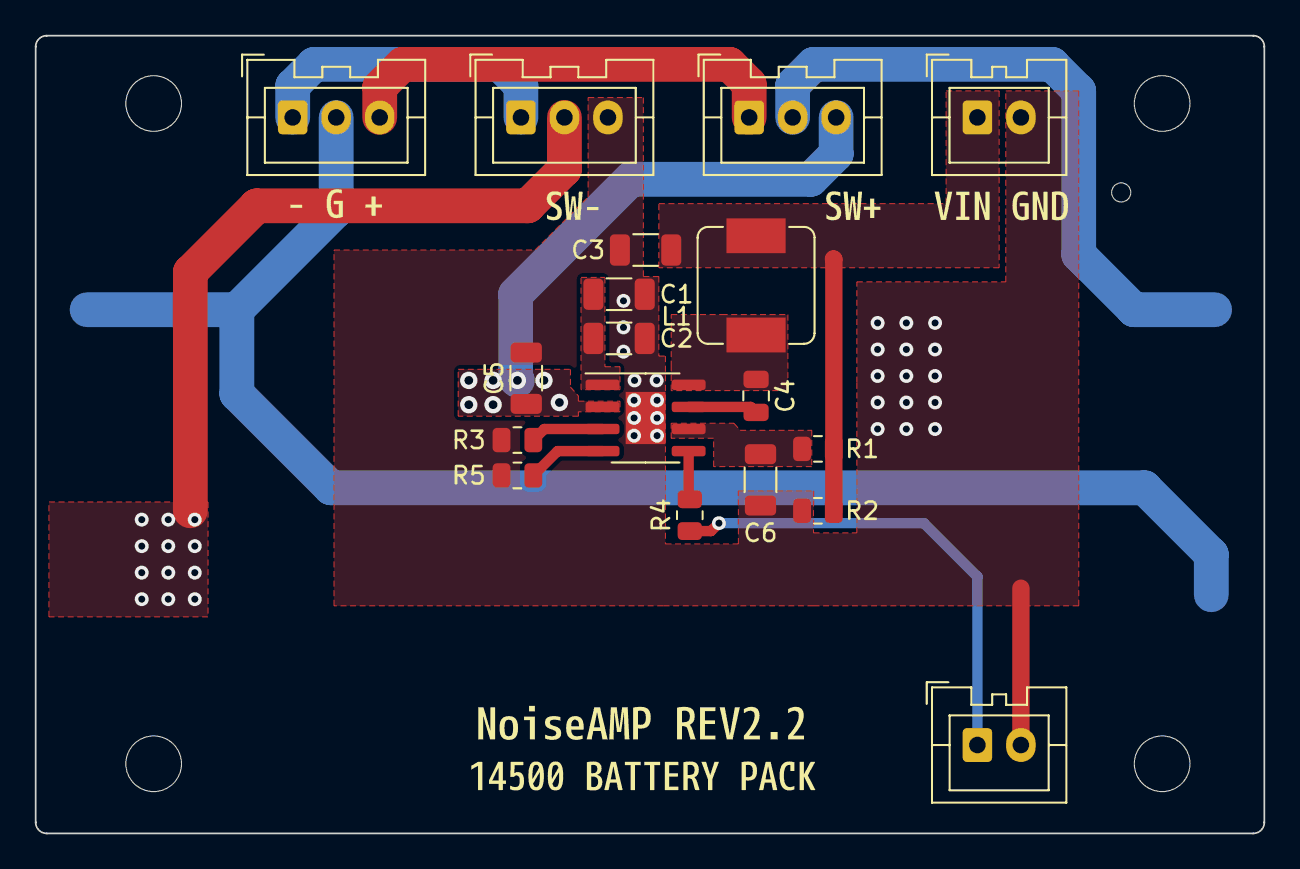
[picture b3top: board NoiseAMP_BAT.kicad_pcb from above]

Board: 2 copper layers, 70.6 x 45.8 mm, 29 parts (1 on the bottom side), 16 nets.

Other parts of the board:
kibuzzard-624F939D: G***; kibuzzard-624F939D
kibuzzard-624F940E: G***; kibuzzard-624F940E
kibuzzard-624F9385: G***; kibuzzard-624F9385
kibuzzard-624F9417: G***; kibuzzard-624F9417
kibuzzard-624F9427: G***; kibuzzard-624F9427
kibuzzard-624F9438: G***; kibuzzard-624F9438

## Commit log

2022-10-27 update test figures and README
2022-10-27 Add V2.3 Design files and update EmoeNAP dev plans
2022-11-02 fix arch bugs
2022-11-19 Update EmoeNAP PCB files
2023-04-30 Update EmoeNAP design
2023-07-04 Update progress and notes
